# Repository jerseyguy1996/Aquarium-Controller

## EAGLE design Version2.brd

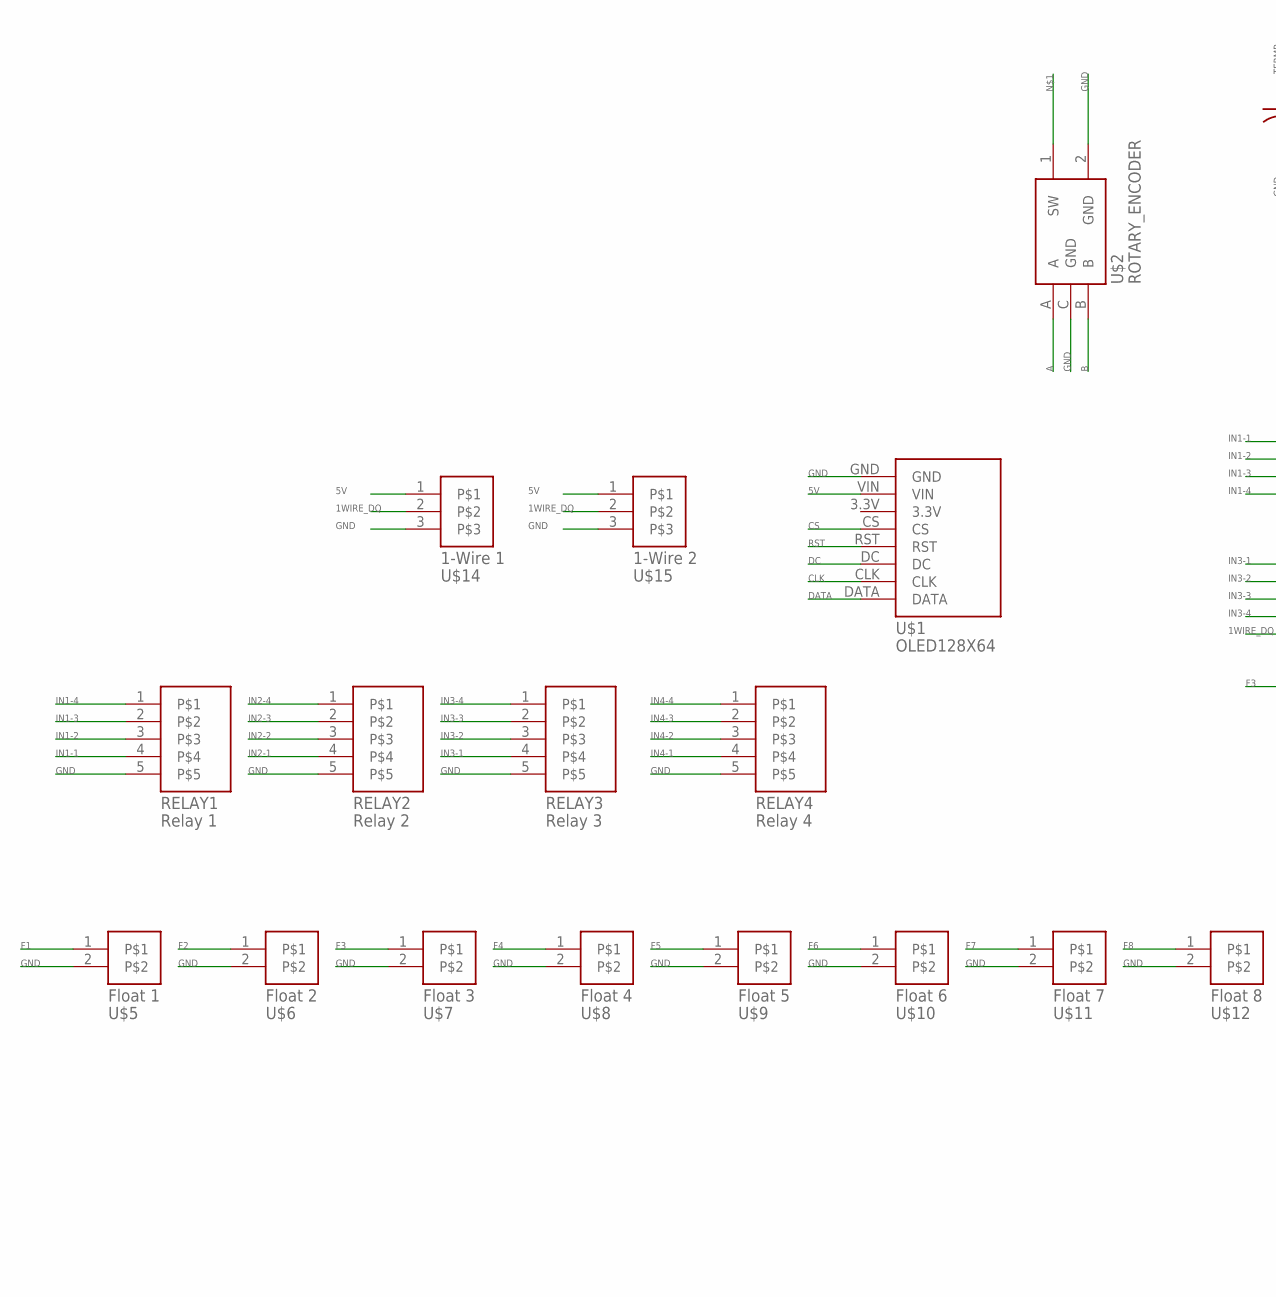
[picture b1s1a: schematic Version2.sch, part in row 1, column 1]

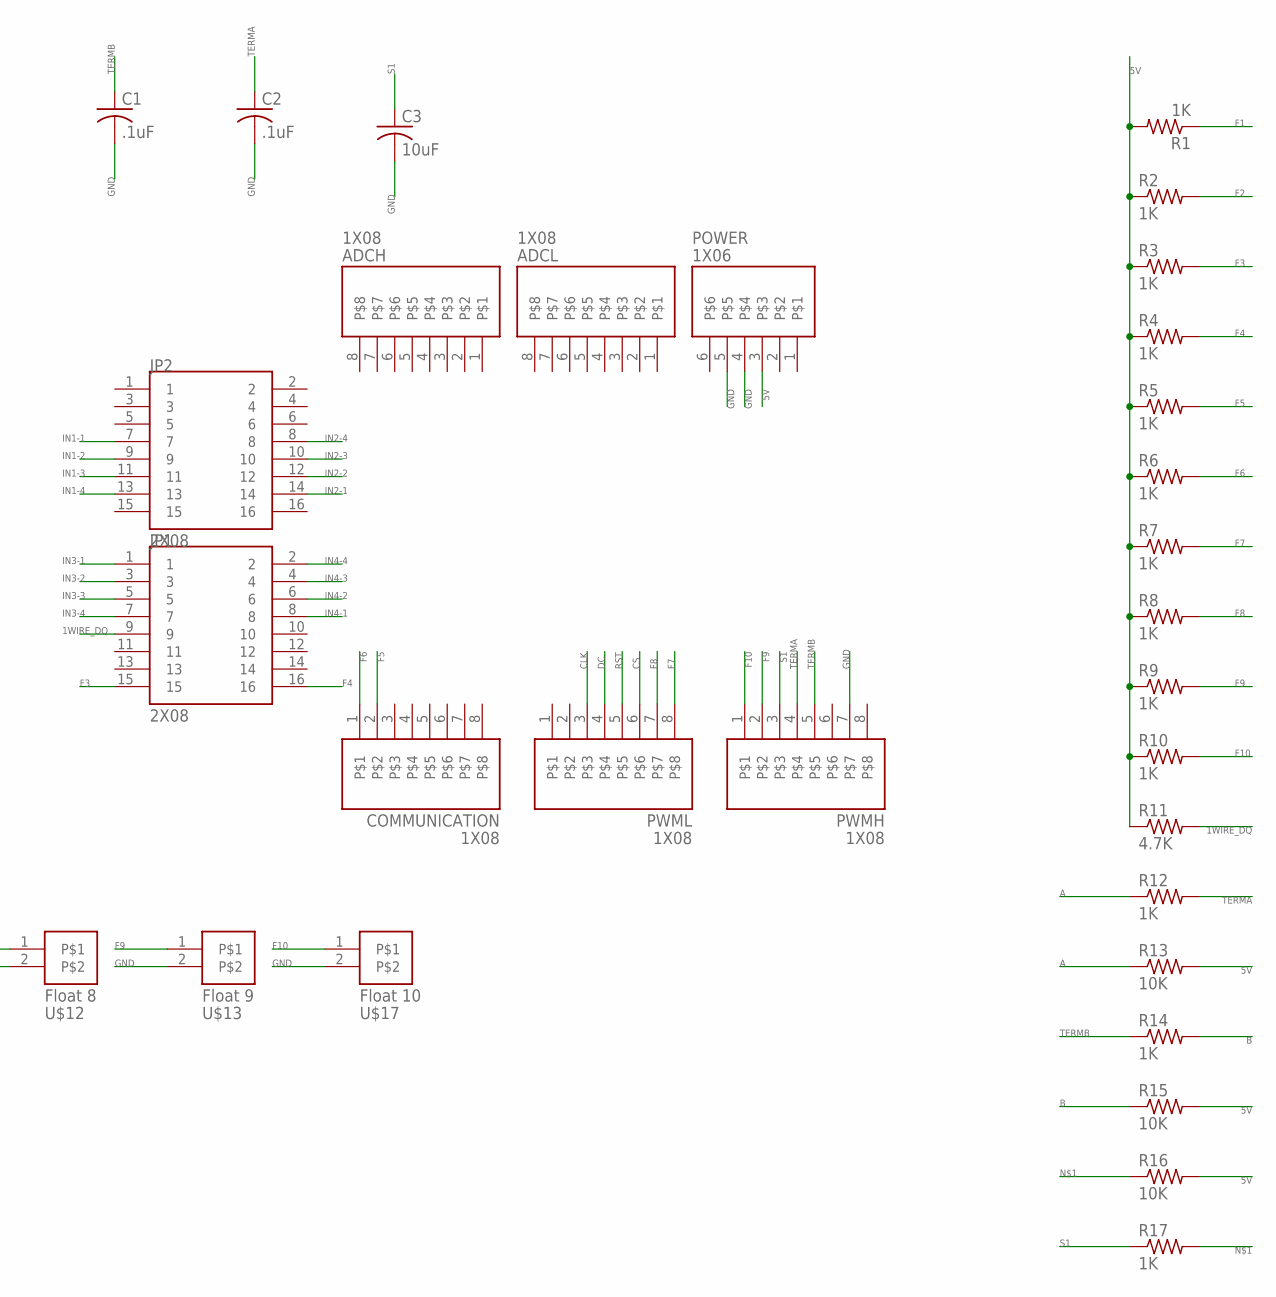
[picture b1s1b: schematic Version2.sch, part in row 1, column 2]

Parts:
ADCH: 1X08; 1X08_SMT
ADCL: 1X08; 1X08_SMT
C1, C2: .1uF; C0805K
C3: 10uF; C0805K
COMMUNICATION: 1X08; 1X08_SMT
JP1, JP2: 2X08; 2X08_SMT
POWER: 1X06; 1X06_SMT
PWMH: 1X08; 1X08_SMT
PWML: 1X08; 1X08_SMT
R1, R2, R3, R4, R5, R6, R7, R8, R9, R10, R12, R14, R17: 1K; R0805
R11: 4.7K; R0805
R13, R15, R16: 10K; R0805
RELAY1: Relay 1; 5PIN-MOLEX-HEADER-W-PEGS
RELAY2: Relay 2; 5PIN-MOLEX-HEADER-W-PEGS
RELAY3: Relay 3; 5PIN-MOLEX-HEADER-W-PEGS
RELAY4: Relay 4; 5PIN-MOLEX-HEADER-W-PEGS
U$1: OLED128X64
U$2: ROTARY_ENCODER; PEC11-4215F-S24
U$5: Float 1; 2PIN-MOLEX-HEADER-W-PEGS
U$6: Float 2; 2PIN-MOLEX-HEADER-W-PEGS
U$7: Float 3; 2PIN-MOLEX-HEADER-W-PEGS
U$8: Float 4; 2PIN-MOLEX-HEADER-W-PEGS
U$9: Float 5; 2PIN-MOLEX-HEADER-W-PEGS
U$10: Float 6; 2PIN-MOLEX-HEADER-W-PEGS
U$11: Float 7; 2PIN-MOLEX-HEADER-W-PEGS
U$12: Float 8; 2PIN-MOLEX-HEADER-W-PEGS
U$13: Float 9; 2PIN-MOLEX-HEADER-W-PEGS
U$14: 1-Wire 1; 3PIN-MOLEX-HEADER-W-PEGS
U$15: 1-Wire 2; 3PIN-MOLEX-HEADER-W-PEGS
U$17: Float 10; 2PIN-MOLEX-HEADER-W-PEGS

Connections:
1WIRE_DQ: JP1.9, R11.2, U$14.2, U$15.2
5V: POWER.3, R1.2, R2.1, R3.1, R4.1, R5.1, R6.1, R7.1, R8.1, R9.1, R10.1, R11.1, R13.2, R15.2, R16.2, U$1.VIN, U$14.1, U$15.1
A: R12.1, R13.1, U$2.A
B: R14.2, R15.1, U$2.B
CLK: PWML.3, U$1.CLK
CS: PWML.6, U$1.CS
DATA: U$1.DATA
DC: PWML.4, U$1.DC
F1: R1.1, U$5.1
F2: R2.2, U$6.1
F3: JP1.15, R3.2, U$7.1
F4: JP1.16, R4.2, U$8.1
F5: COMMUNICATION.2, R5.2, U$9.1
F6: COMMUNICATION.1, R6.2, U$10.1
F7: PWML.8, R7.2, U$11.1
F8: PWML.7, R8.2, U$12.1
F9: PWMH.2, R9.2, U$13.1
F10: PWMH.1, R10.2, U$17.1
GND: C1.2, C2.2, C3.2, POWER.4, POWER.5, PWMH.7, RELAY1.5, RELAY2.5, RELAY3.5, RELAY4.5, U$1.GND, U$2.2 (GND), U$2.C (GND), U$5.2, U$6.2, U$7.2, U$8.2, U$9.2, U$10.2, U$11.2, U$12.2, U$13.2, U$14.3, U$15.3, U$17.2
IN1-1: JP2.7, RELAY1.4
IN1-2: JP2.9, RELAY1.3
IN1-3: JP2.11, RELAY1.2
IN1-4: JP2.13, RELAY1.1
IN2-1: JP2.14, RELAY2.4
IN2-2: JP2.12, RELAY2.3
IN2-3: JP2.10, RELAY2.2
IN2-4: JP2.8, RELAY2.1
IN3-1: JP1.1, RELAY3.4
IN3-2: JP1.3, RELAY3.3
IN3-3: JP1.5, RELAY3.2
IN3-4: JP1.7, RELAY3.1
IN4-1: JP1.8, RELAY4.4
IN4-2: JP1.6, RELAY4.3
IN4-3: JP1.4, RELAY4.2
IN4-4: JP1.2, RELAY4.1
unnamed: R16.1, R17.2, U$2.1 (SW)
RST: PWML.5, U$1.RST
S1: C3.1, PWMH.3, R17.1
TERMA: C2.1, PWMH.4, R12.2
TERMB: C1.1, PWMH.5, R14.1

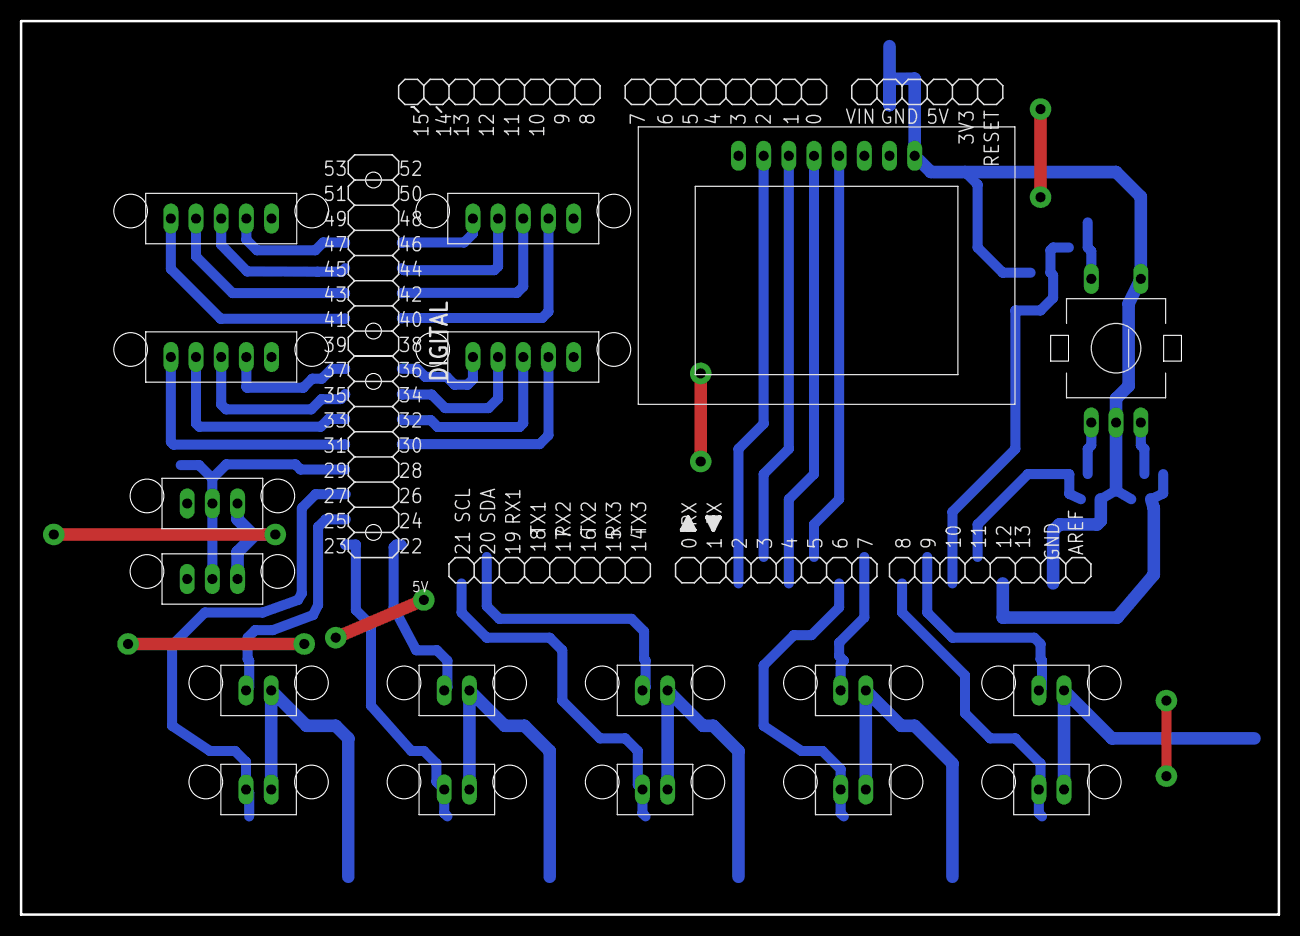
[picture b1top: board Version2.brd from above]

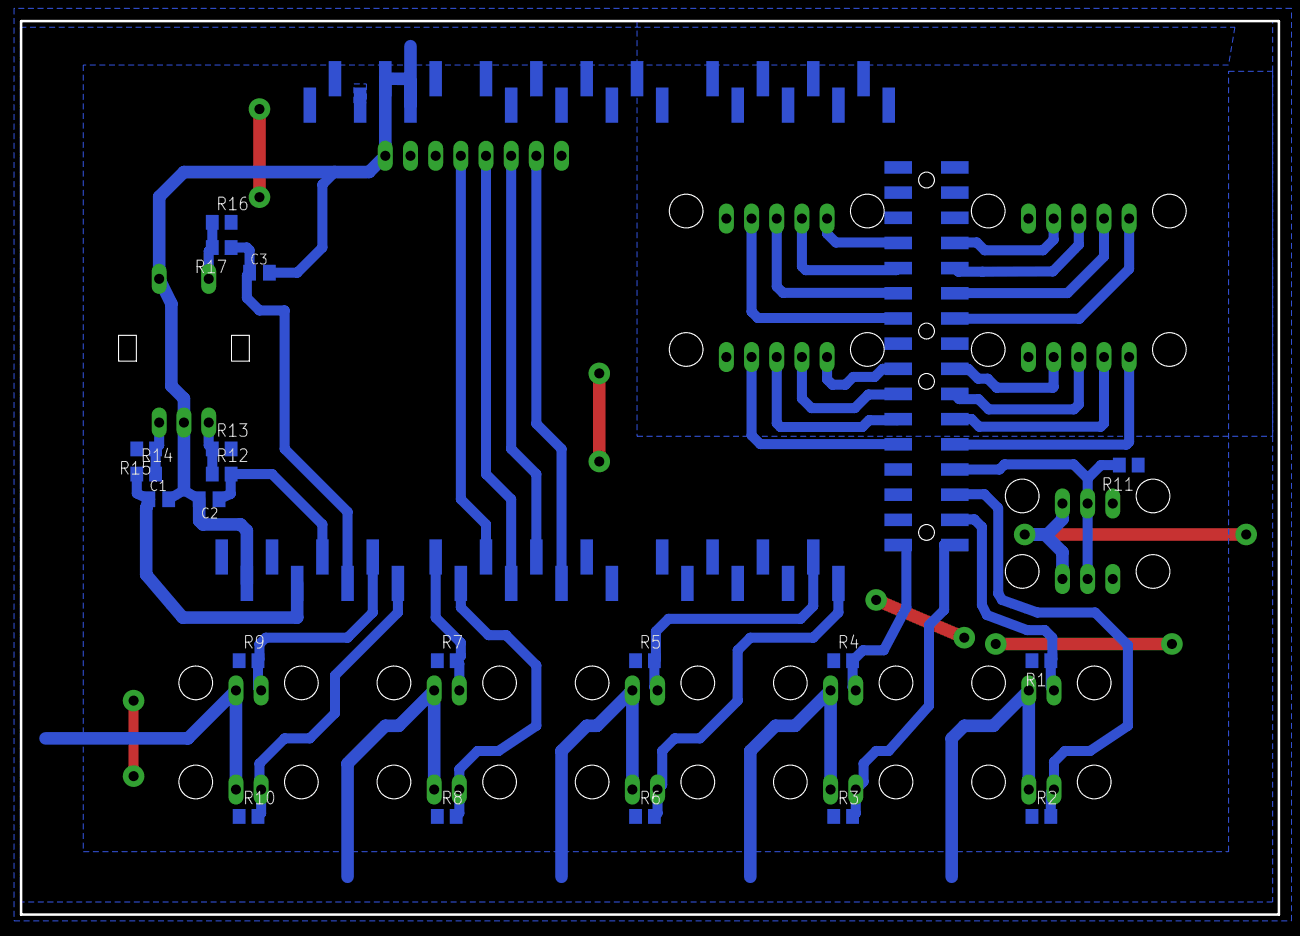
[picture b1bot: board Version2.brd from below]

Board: 2 copper layers, 126.9 x 90.2 mm, 46 parts (20 on the bottom side), 39 nets.

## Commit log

2014-10-11 Aquarium Controller
    Working on building the schematic from the board to enable
    forward/backward annotation
2014-10-16 still making the schematic and board consistent
2015-03-15 Freeing up SPI pins
    This version frees up the SPI pins on the mega so that I can plug in a
    wifi module for internet control and monitoring.
